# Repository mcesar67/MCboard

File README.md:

# MCboard

A parametric solderable protoboard. A Python script writes the KiCad project and the files a PCB fab needs, for any
number of rows and columns. A second script takes a board with the parts of a circuit placed on it, and says which
solder jumpers to close and which wires to add.

| Top | Bottom | Top with `--top smt` |
|---|---|---|
|  |  |  |

*A 14x13 board, rendered by KiCad.*

**Status.** The output passes KiCad's DRC against the fab rules, and the Gerbers match KiCad's own export. See
[Limits](#limits).

**[User manual](docs/MANUAL.md)**: generating a board, and planning a circuit on it, step by step.

## The pattern

Like a breadboard, but soldered, and every connection between groups is your choice. By default the pattern repeats
every 6 rows:

```text
       1   2   3   4
  A    o---o---o---o---   bus: one horizontal track across the board
       x   x   x   x      chevron solder jumper, open until you bridge it
  B    o   o   o   o      2-contact group
  C    o   o   o   o        a vertical strip per column
       x   x   x   x
  D    o   o   o   o      3-contact group
  E    o   o   o   o        a vertical strip per column
  F    o   o   o   o
       x   x   x   x
  G    o---o---o---o---   the next bus
```

Close a 2-3 chevron and the two groups become a strip of 5, as on a breadboard; close the others to reach a bus. All
tracks are on the bottom side, under solder mask. `--pattern` sets other arrangements, such as `b+5`, `b+3+2+2b+5` or
`classic`, a breadboard with two rails; `--top smt` adds chevrons and islands on the top side for SMD parts. See
[the manual](docs/MANUAL.md#15-row-pattern).

## Quick start

You need Python 3 and nothing else; KiCad is needed only to check the board or place a circuit on it.

```bash
cd protoboard_generator
python3 generate_protoboard.py --cols 30 --rows 61 --fab jlcpcb
```

This writes the KiCad project, a zip for the fab and an A4 PDF of both sides, like those in [`examples/`](examples/). Upload the zip and order a **2-layer
board, 1 oz copper**.

To plan a circuit, generate the board with `--working-copy`, which also writes `<name>_working.kicad_pcb`. In KiCad,
update that file from your schematic, place the parts with their pins on the holes, save, and run:

```bash
python3 plan_board.py <folder>/<name>_working.kicad_pcb
```

It prints which chevrons to close and which wires to add, and writes a PDF with both sides marked. The same is
available as a button in KiCad's PCB editor, installed with `python3 install_kicad_plugin.py`, and a second button
applies the plan to the working copy, so that KiCad's ratsnest shows what is left to wire. A third clears both, and a
fourth, for wiring by hand, updates the ratsnest after each chevron or wire you draw yourself, without planning. They
are described in [the manual](docs/MANUAL.md#21-what-the-plan-gives-you).

Everything else, options, mounting holes, checking a board, reading the plan and drawing part of the wiring yourself,
is in the [user manual](docs/MANUAL.md).

## Limits

- With `--top smt`, excess solder can close a chevron hidden under a part.
- The planner is a heuristic: it always gives the same plan for the same board, but that plan may not have the fewest
  wires or chevrons, and placement decides whether a plan exists at all.
- The KiCad buttons need KiCad 9.0 or later with its API turned on, and fetch the `kicad-python` package the first
  time. They have been tried on KiCad 9 and 10, on Linux and Windows 11, but not on macOS.
- Text in very dense characters, such as CJK at 1 mm, may fill in when printed.
- There is no automated test suite yet.

## Repository layout

| Path | Contents |
|---|---|
| `protoboard_generator/generate_protoboard.py` | The generator's entry point |
| `protoboard_generator/plan_board.py` | The planner's entry point |
| `protoboard_generator/install_kicad_plugin.py`, `kicad_plugin/` | The KiCad buttons |
| `protoboard_generator/protoboard/` | The code. Its `__init__.py` is the reading guide |
| `protoboard_generator/rules/`, `fonts/` | Fab rules and the stroke font, see `NOTICE.md` |
| `examples/` | Generated boards ready to open or order: a classic breadboard, the default, and the default with `--top smt` |
| `tests/t555/` | Test boards for the planner: a 555 circuit, imported and placed |
| `docs/MANUAL.md` | User manual: generating a board, then planning a circuit |
| `docs/DESIGN.md` | Design notes: why the pattern is what it is, every dimension, what was rejected, how to check changes |

## Licence

Copyright (C) 2026 [mcesar67](https://github.com/mcesar67).

The code and documentation were written with the help of Claude (Anthropic), under the author's direction.

GPL-3.0-or-later, see [`LICENSE`](LICENSE). Third-party material and its licences are listed in [`NOTICE.md`](NOTICE.md).
There is no warranty of any kind: check a board before you pay for it.

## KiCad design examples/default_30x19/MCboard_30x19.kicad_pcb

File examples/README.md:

# Examples

Boards generated as they are, ready to open in KiCad or to order. Each folder has the KiCad project, the zip for the fab
and the A4 drawing. They were made with `--fab generic`, the default, which satisfies both JLCPCB and PCBWay, and
are in KiCad 10 format; add `--kicad 9` to the commands below for KiCad 9.

| Folder | Board | Size |
|---|---|---|
| `classic_64x20/` | A classic breadboard: two rails at each edge, two strips of 5 per column, no mounting holes | 170.02 x 58.26 mm |
| `default_30x19/` | The default pattern, a hole in each corner, `--silk outline` | 81.66 x 62.72 mm |
| `smt_30x19/` | The same with `--top smt`, with the default `--silk bars` | 81.66 x 62.72 mm |

To make them again, from the `protoboard_generator` folder:

```bash
python3 generate_protoboard.py --cols 64 --rows 20 --pattern classic --no-mount-holes --margin-plain 5 -o ../examples/classic_64x20/
python3 generate_protoboard.py --cols 30 --rows 19 --mount-x 2 --mount-y 0 --silk outline -o ../examples/default_30x19/
python3 generate_protoboard.py --cols 30 --rows 19 --mount-x 2 --mount-y 0 --top smt -o ../examples/smt_30x19/
```

`--margin-plain 5` makes room for the name, which does not fit in the 4 mm margin of a board with no mounting holes.
`--mount-x 2 --mount-y 0` puts two holes on the top and bottom sides and none on the others, so they end up in the
corners. The options are explained in the [user manual](../docs/MANUAL.md).

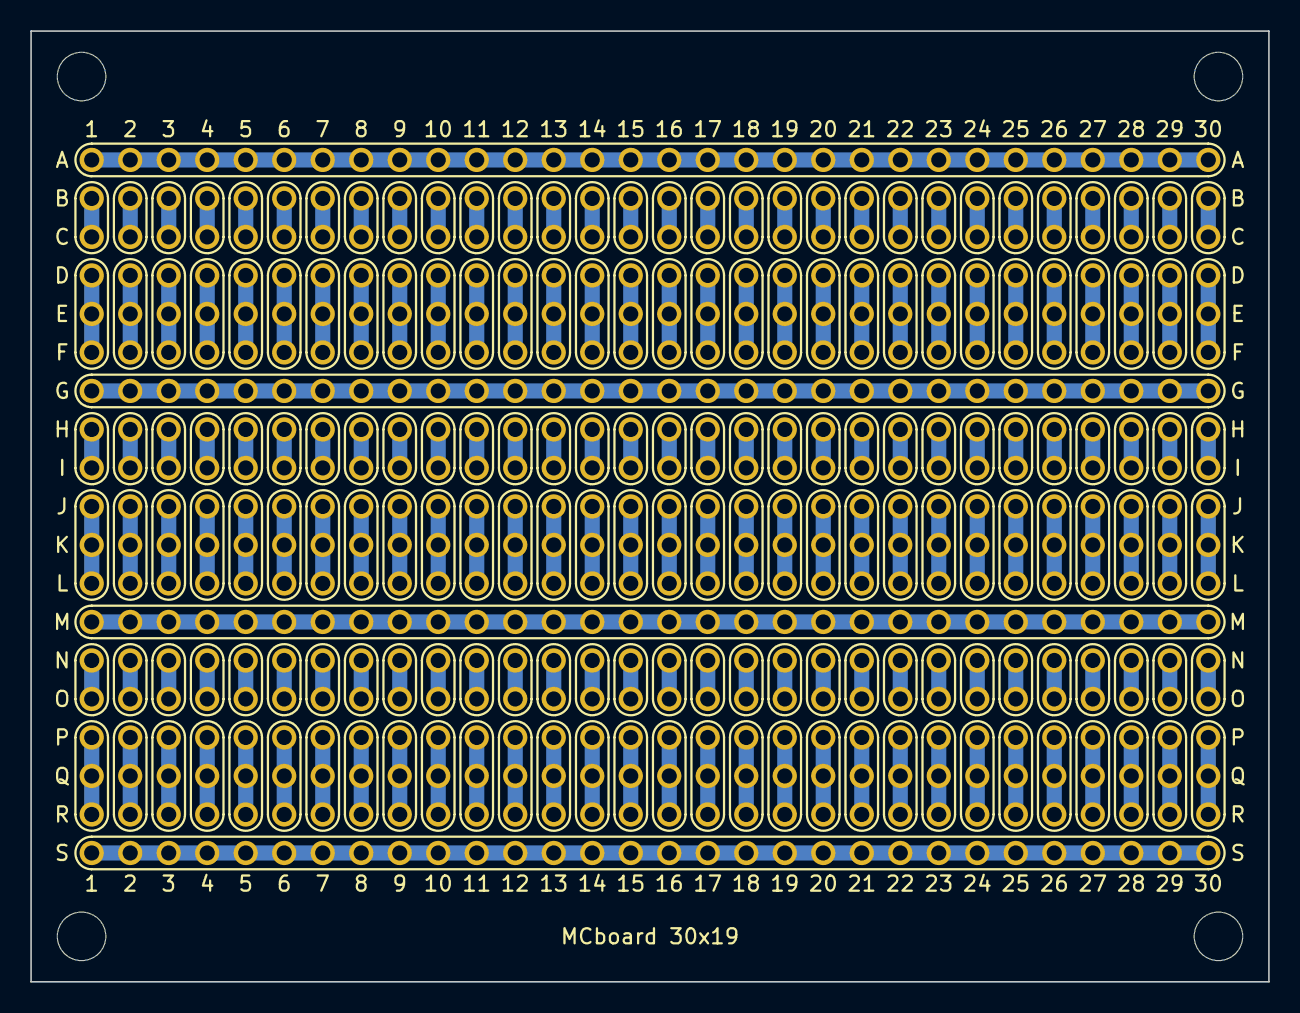
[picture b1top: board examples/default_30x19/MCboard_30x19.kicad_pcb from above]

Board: 2 copper layers, 81.7 x 62.7 mm, 844 parts (0 on the bottom side), 184 nets.

Parts:
PBH1, PBH2, PBH3, PBH4, PBH5, PBH6, PBH7, PBH8, PBH9, PBH10, PBH11, PBH12, PBH13, PBH14, PBH15, PBH16, PBH17, PBH18, PBH19, PBH20, PBH21, PBH22, PBH23, PBH24, PBH25, PBH26, PBH27, PBH28, PBH29, PBH30, PBH31, PBH32, PBH33, PBH34, PBH35, PBH36, PBH37, PBH38, PBH39, PBH40, PBH41, PBH42, PBH43, PBH44, PBH45, PBH46, PBH47, PBH48, PBH49, PBH50, PBH51, PBH52, PBH53, PBH54, PBH55, PBH56, PBH57, PBH58, PBH59, PBH60, PBH61, PBH62, PBH63, PBH64, PBH65, PBH66, PBH67, PBH68, PBH69, PBH70, PBH71, PBH72, PBH73, PBH74, PBH75, PBH76, PBH77, PBH78, PBH79, PBH80, PBH81, PBH82, PBH83, PBH84, PBH85, PBH86, PBH87, PBH88, PBH89, PBH90, PBH91, PBH92, PBH93, PBH94, PBH95, PBH96, PBH97, PBH98, PBH99, PBH100, PBH101, PBH102, PBH103, PBH104, PBH105, PBH106, PBH107, PBH108, PBH109, PBH110, PBH111, PBH112, PBH113, PBH114, PBH115, PBH116, PBH117, PBH118, PBH119, PBH120, PBH121, PBH122, PBH123, PBH124, PBH125, PBH126, PBH127, PBH128, PBH129, PBH130, PBH131, PBH132, PBH133, PBH134, PBH135, PBH136, PBH137, PBH138, PBH139, PBH140, PBH141, PBH142, PBH143, PBH144, PBH145, PBH146, PBH147, PBH148, PBH149, PBH150, PBH151, PBH152, PBH153, PBH154, PBH155, PBH156, PBH157, PBH158, PBH159, PBH160, PBH161, PBH162, PBH163, PBH164, PBH165, PBH166, PBH167, PBH168, PBH169, PBH170, PBH171, PBH172, PBH173, PBH174, PBH175, PBH176, PBH177, PBH178, PBH179, PBH180, PBH181, PBH182, PBH183, PBH184, PBH185, PBH186, PBH187, PBH188, PBH189, PBH190, PBH191, PBH192, PBH193, PBH194, PBH195, PBH196, PBH197, PBH198, PBH199, PBH200, PBH201, PBH202, PBH203, PBH204, PBH205, PBH206, PBH207, PBH208, PBH209, PBH210, PBH211, PBH212, PBH213, PBH214, PBH215, PBH216, PBH217, PBH218, PBH219, PBH220, PBH221, PBH222, PBH223, PBH224, PBH225, PBH226, PBH227, PBH228, PBH229, PBH230, PBH231, PBH232, PBH233, PBH234, PBH235, PBH236, PBH237, PBH238, PBH239, PBH240, PBH241, PBH242, PBH243, PBH244, PBH245, PBH246, PBH247, PBH248, PBH249, PBH250, PBH251, PBH252, PBH253, PBH254, PBH255, PBH256, PBH257, PBH258, PBH259, PBH260, PBH261, PBH262, PBH263, PBH264, PBH265, PBH266, PBH267, PBH268, PBH269, PBH270, PBH271, PBH272, PBH273, PBH274, PBH275, PBH276, PBH277, PBH278, PBH279, PBH280, PBH281, PBH282, PBH283, PBH284, PBH285, PBH286, PBH287, PBH288, PBH289, PBH290, PBH291, PBH292, PBH293, PBH294, PBH295, PBH296, PBH297, PBH298, PBH299, PBH300, PBH301, PBH302, PBH303, PBH304, PBH305, PBH306, PBH307, PBH308, PBH309, PBH310, PBH311, PBH312, PBH313, PBH314, PBH315, PBH316, PBH317, PBH318, PBH319, PBH320, PBH321, PBH322, PBH323, PBH324, PBH325, PBH326, PBH327, PBH328, PBH329, PBH330, PBH331, PBH332, PBH333, PBH334, PBH335, PBH336, PBH337, PBH338, PBH339, PBH340, PBH341, PBH342, PBH343, PBH344, PBH345, PBH346, PBH347, PBH348, PBH349, PBH350, PBH351, PBH352, PBH353, PBH354, PBH355, PBH356, PBH357, PBH358, PBH359, PBH360, PBH361, PBH362, PBH363, PBH364, PBH365, PBH366, PBH367, PBH368, PBH369, PBH370, PBH371, PBH372, PBH373, PBH374, PBH375, PBH376, PBH377, PBH378, PBH379, PBH380, PBH381, PBH382, PBH383, PBH384, PBH385, PBH386, PBH387, PBH388, PBH389, PBH390, PBH391, PBH392, PBH393, PBH394, PBH395, PBH396, PBH397, PBH398, PBH399, PBH400, PBH401, PBH402, PBH403, PBH404, PBH405, PBH406, PBH407, PBH408, PBH409, PBH410, PBH411, PBH412, PBH413, PBH414, PBH415, PBH416, PBH417, PBH418, PBH419, PBH420, PBH421, PBH422, PBH423, PBH424, PBH425, PBH426, PBH427, PBH428, PBH429, PBH430, PBH431, PBH432, PBH433, PBH434, PBH435, PBH436, PBH437, PBH438, PBH439, PBH440, PBH441, PBH442, PBH443, PBH444, PBH445, PBH446, PBH447, PBH448, PBH449, PBH450, PBH451, PBH452, PBH453, PBH454, PBH455, PBH456, PBH457, PBH458, PBH459, PBH460, PBH461, PBH462, PBH463, PBH464, PBH465, PBH466, PBH467, PBH468, PBH469, PBH470, PBH471, PBH472, PBH473, PBH474, PBH475, PBH476, PBH477, PBH478, PBH479, PBH480, PBH481, PBH482, PBH483, PBH484, PBH485, PBH486, PBH487, PBH488, PBH489, PBH490, PBH491, PBH492, PBH493, PBH494, PBH495, PBH496, PBH497, PBH498, PBH499, PBH500, PBH501, PBH502, PBH503, PBH504, PBH505, PBH506, PBH507, PBH508, PBH509, PBH510, PBH511, PBH512, PBH513, PBH514, PBH515, PBH516, PBH517, PBH518, PBH519, PBH520, PBH521, PBH522, PBH523, PBH524, PBH525, PBH526, PBH527, PBH528, PBH529, PBH530, PBH531, PBH532, PBH533, PBH534, PBH535, PBH536, PBH537, PBH538, PBH539, PBH540, PBH541, PBH542, PBH543, PBH544, PBH545, PBH546, PBH547, PBH548, PBH549, PBH550, PBH551, PBH552, PBH553, PBH554, PBH555, PBH556, PBH557, PBH558, PBH559, PBH560, PBH561, PBH562, PBH563, PBH564, PBH565, PBH566, PBH567, PBH568, PBH569, PBH570: hole; Hole
PBJP1, PBJP2, PBJP3, PBJP4, PBJP5, PBJP6, PBJP7, PBJP8, PBJP9, PBJP10, PBJP11, PBJP12, PBJP13, PBJP14, PBJP15, PBJP16, PBJP17, PBJP18, PBJP19, PBJP20, PBJP21, PBJP22, PBJP23, PBJP24, PBJP25, PBJP26, PBJP27, PBJP28, PBJP29, PBJP30, PBJP31, PBJP32, PBJP33, PBJP34, PBJP35, PBJP36, PBJP37, PBJP38, PBJP39, PBJP40, PBJP41, PBJP42, PBJP43, PBJP44, PBJP45, PBJP46, PBJP47, PBJP48, PBJP49, PBJP50, PBJP51, PBJP52, PBJP53, PBJP54, PBJP55, PBJP56, PBJP57, PBJP58, PBJP59, PBJP60, PBJP61, PBJP62, PBJP63, PBJP64, PBJP65, PBJP66, PBJP67, PBJP68, PBJP69, PBJP70, PBJP71, PBJP72, PBJP73, PBJP74, PBJP75, PBJP76, PBJP77, PBJP78, PBJP79, PBJP80, PBJP81, PBJP82, PBJP83, PBJP84, PBJP85, PBJP86, PBJP87, PBJP88, PBJP89, PBJP90, PBJP91, PBJP92, PBJP93, PBJP94, PBJP95, PBJP96, PBJP97, PBJP98, PBJP99, PBJP100, PBJP101, PBJP102, PBJP103, PBJP104, PBJP105, PBJP106, PBJP107, PBJP108, PBJP109, PBJP110, PBJP111, PBJP112, PBJP113, PBJP114, PBJP115, PBJP116, PBJP117, PBJP118, PBJP119, PBJP120, PBJP121, PBJP122, PBJP123, PBJP124, PBJP125, PBJP126, PBJP127, PBJP128, PBJP129, PBJP130, PBJP131, PBJP132, PBJP133, PBJP134, PBJP135, PBJP136, PBJP137, PBJP138, PBJP139, PBJP140, PBJP141, PBJP142, PBJP143, PBJP144, PBJP145, PBJP146, PBJP147, PBJP148, PBJP149, PBJP150, PBJP151, PBJP152, PBJP153, PBJP154, PBJP155, PBJP156, PBJP157, PBJP158, PBJP159, PBJP160, PBJP161, PBJP162, PBJP163, PBJP164, PBJP165, PBJP166, PBJP167, PBJP168, PBJP169, PBJP170, PBJP171, PBJP172, PBJP173, PBJP174, PBJP175, PBJP176, PBJP177, PBJP178, PBJP179, PBJP180, PBJP181, PBJP182, PBJP183, PBJP184, PBJP185, PBJP186, PBJP187, PBJP188, PBJP189, PBJP190, PBJP191, PBJP192, PBJP193, PBJP194, PBJP195, PBJP196, PBJP197, PBJP198, PBJP199, PBJP200, PBJP201, PBJP202, PBJP203, PBJP204, PBJP205, PBJP206, PBJP207, PBJP208, PBJP209, PBJP210, PBJP211, PBJP212, PBJP213, PBJP214, PBJP215, PBJP216, PBJP217, PBJP218, PBJP219, PBJP220, PBJP221, PBJP222, PBJP223, PBJP224, PBJP225, PBJP226, PBJP227, PBJP228, PBJP229, PBJP230, PBJP231, PBJP232, PBJP233, PBJP234, PBJP235, PBJP236, PBJP237, PBJP238, PBJP239, PBJP240, PBJP241, PBJP242, PBJP243, PBJP244, PBJP245, PBJP246, PBJP247, PBJP248, PBJP249, PBJP250, PBJP251, PBJP252, PBJP253, PBJP254, PBJP255, PBJP256, PBJP257, PBJP258, PBJP259, PBJP260, PBJP261, PBJP262, PBJP263, PBJP264, PBJP265, PBJP266, PBJP267, PBJP268, PBJP269, PBJP270: chevron; ChevronJumper
PBMH1, PBMH2, PBMH3, PBMH4: mounting hole; MountingHole

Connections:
BUS_R1: PBH1.1, PBH20.1, PBH39.1, PBH58.1, PBH77.1, PBH96.1, PBH115.1, PBH134.1, PBH153.1, PBH172.1, PBH191.1, PBH210.1, PBH229.1, PBH248.1, PBH267.1, PBH286.1, PBH305.1, PBH324.1, PBH343.1, PBH362.1, PBH381.1, PBH400.1, PBH419.1, PBH438.1, PBH457.1, PBH476.1, PBH495.1, PBH514.1, PBH533.1, PBH552.1, PBJP1.1, PBJP10.1, PBJP19.1, PBJP28.1, PBJP37.1, PBJP46.1, PBJP55.1, PBJP64.1, PBJP73.1, PBJP82.1, PBJP91.1, PBJP100.1, PBJP109.1, PBJP118.1, PBJP127.1, PBJP136.1, PBJP145.1, PBJP154.1, PBJP163.1, PBJP172.1, PBJP181.1, PBJP190.1, PBJP199.1, PBJP208.1, PBJP217.1, PBJP226.1, PBJP235.1, PBJP244.1, PBJP253.1, PBJP262.1
BUS_R7: PBH7.1, PBH26.1, PBH45.1, PBH64.1, PBH83.1, PBH102.1, PBH121.1, PBH140.1, PBH159.1, PBH178.1, PBH197.1, PBH216.1, PBH235.1, PBH254.1, PBH273.1, PBH292.1, PBH311.1, PBH330.1, PBH349.1, PBH368.1, PBH387.1, PBH406.1, PBH425.1, PBH444.1, PBH463.1, PBH482.1, PBH501.1, PBH520.1, PBH539.1, PBH558.1, PBJP3.2, PBJP4.1, PBJP12.2, PBJP13.1, PBJP21.2, PBJP22.1, PBJP30.2, PBJP31.1, PBJP39.2, PBJP40.1, PBJP48.2, PBJP49.1, PBJP57.2, PBJP58.1, PBJP66.2, PBJP67.1, PBJP75.2, PBJP76.1, PBJP84.2, PBJP85.1, PBJP93.2, PBJP94.1, PBJP102.2, PBJP103.1, PBJP111.2, PBJP112.1, PBJP120.2, PBJP121.1, PBJP129.2, PBJP130.1, PBJP138.2, PBJP139.1, PBJP147.2, PBJP148.1, PBJP156.2, PBJP157.1, PBJP165.2, PBJP166.1, PBJP174.2, PBJP175.1, PBJP183.2, PBJP184.1, PBJP192.2, PBJP193.1, PBJP201.2, PBJP202.1, PBJP210.2, PBJP211.1, PBJP219.2, PBJP220.1, PBJP228.2, PBJP229.1, PBJP237.2, PBJP238.1, PBJP246.2, PBJP247.1, PBJP255.2, PBJP256.1, PBJP264.2, PBJP265.1
BUS_R13: PBH13.1, PBH32.1, PBH51.1, PBH70.1, PBH89.1, PBH108.1, PBH127.1, PBH146.1, PBH165.1, PBH184.1, PBH203.1, PBH222.1, PBH241.1, PBH260.1, PBH279.1, PBH298.1, PBH317.1, PBH336.1, PBH355.1, PBH374.1, PBH393.1, PBH412.1, PBH431.1, PBH450.1, PBH469.1, PBH488.1, PBH507.1, PBH526.1, PBH545.1, PBH564.1, PBJP6.2, PBJP7.1, PBJP15.2, PBJP16.1, PBJP24.2, PBJP25.1, PBJP33.2, PBJP34.1, PBJP42.2, PBJP43.1, PBJP51.2, PBJP52.1, PBJP60.2, PBJP61.1, PBJP69.2, PBJP70.1, PBJP78.2, PBJP79.1, PBJP87.2, PBJP88.1, PBJP96.2, PBJP97.1, PBJP105.2, PBJP106.1, PBJP114.2, PBJP115.1, PBJP123.2, PBJP124.1, PBJP132.2, PBJP133.1, PBJP141.2, PBJP142.1, PBJP150.2, PBJP151.1, PBJP159.2, PBJP160.1, PBJP168.2, PBJP169.1, PBJP177.2, PBJP178.1, PBJP186.2, PBJP187.1, PBJP195.2, PBJP196.1, PBJP204.2, PBJP205.1, PBJP213.2, PBJP214.1, PBJP222.2, PBJP223.1, PBJP231.2, PBJP232.1, PBJP240.2, PBJP241.1, PBJP249.2, PBJP250.1, PBJP258.2, PBJP259.1, PBJP267.2, PBJP268.1
BUS_R19: PBH19.1, PBH38.1, PBH57.1, PBH76.1, PBH95.1, PBH114.1, PBH133.1, PBH152.1, PBH171.1, PBH190.1, PBH209.1, PBH228.1, PBH247.1, PBH266.1, PBH285.1, PBH304.1, PBH323.1, PBH342.1, PBH361.1, PBH380.1, PBH399.1, PBH418.1, PBH437.1, PBH456.1, PBH475.1, PBH494.1, PBH513.1, PBH532.1, PBH551.1, PBH570.1, PBJP9.2, PBJP18.2, PBJP27.2, PBJP36.2, PBJP45.2, PBJP54.2, PBJP63.2, PBJP72.2, PBJP81.2, PBJP90.2, PBJP99.2, PBJP108.2, PBJP117.2, PBJP126.2, PBJP135.2, PBJP144.2, PBJP153.2, PBJP162.2, PBJP171.2, PBJP180.2, PBJP189.2, PBJP198.2, PBJP207.2, PBJP216.2, PBJP225.2, PBJP234.2, PBJP243.2, PBJP252.2, PBJP261.2, PBJP270.2
C1_R2: PBH2.1, PBH3.1, PBJP1.2, PBJP2.1
C1_R4: PBH4.1, PBH5.1, PBH6.1, PBJP2.2, PBJP3.1
C1_R8: PBH8.1, PBH9.1, PBJP4.2, PBJP5.1
C1_R10: PBH10.1, PBH11.1, PBH12.1, PBJP5.2, PBJP6.1
C1_R14: PBH14.1, PBH15.1, PBJP7.2, PBJP8.1
C1_R16: PBH16.1, PBH17.1, PBH18.1, PBJP8.2, PBJP9.1
C2_R2: PBH21.1, PBH22.1, PBJP10.2, PBJP11.1
C2_R4: PBH23.1, PBH24.1, PBH25.1, PBJP11.2, PBJP12.1
C2_R8: PBH27.1, PBH28.1, PBJP13.2, PBJP14.1
C2_R10: PBH29.1, PBH30.1, PBH31.1, PBJP14.2, PBJP15.1
C2_R14: PBH33.1, PBH34.1, PBJP16.2, PBJP17.1
C2_R16: PBH35.1, PBH36.1, PBH37.1, PBJP17.2, PBJP18.1
C3_R2: PBH40.1, PBH41.1, PBJP19.2, PBJP20.1
C3_R4: PBH42.1, PBH43.1, PBH44.1, PBJP20.2, PBJP21.1
C3_R8: PBH46.1, PBH47.1, PBJP22.2, PBJP23.1
C3_R10: PBH48.1, PBH49.1, PBH50.1, PBJP23.2, PBJP24.1
C3_R14: PBH52.1, PBH53.1, PBJP25.2, PBJP26.1
C3_R16: PBH54.1, PBH55.1, PBH56.1, PBJP26.2, PBJP27.1
C4_R2: PBH59.1, PBH60.1, PBJP28.2, PBJP29.1
C4_R4: PBH61.1, PBH62.1, PBH63.1, PBJP29.2, PBJP30.1
C4_R8: PBH65.1, PBH66.1, PBJP31.2, PBJP32.1
C4_R10: PBH67.1, PBH68.1, PBH69.1, PBJP32.2, PBJP33.1
C4_R14: PBH71.1, PBH72.1, PBJP34.2, PBJP35.1
C4_R16: PBH73.1, PBH74.1, PBH75.1, PBJP35.2, PBJP36.1
C5_R2: PBH78.1, PBH79.1, PBJP37.2, PBJP38.1
C5_R4: PBH80.1, PBH81.1, PBH82.1, PBJP38.2, PBJP39.1
C5_R8: PBH84.1, PBH85.1, PBJP40.2, PBJP41.1
C5_R10: PBH86.1, PBH87.1, PBH88.1, PBJP41.2, PBJP42.1
C5_R14: PBH90.1, PBH91.1, PBJP43.2, PBJP44.1
C5_R16: PBH92.1, PBH93.1, PBH94.1, PBJP44.2, PBJP45.1
C6_R2: PBH97.1, PBH98.1, PBJP46.2, PBJP47.1
C6_R4: PBH99.1, PBH100.1, PBH101.1, PBJP47.2, PBJP48.1
C6_R8: PBH103.1, PBH104.1, PBJP49.2, PBJP50.1
C6_R10: PBH105.1, PBH106.1, PBH107.1, PBJP50.2, PBJP51.1
C6_R14: PBH109.1, PBH110.1, PBJP52.2, PBJP53.1
C6_R16: PBH111.1, PBH112.1, PBH113.1, PBJP53.2, PBJP54.1
C7_R2: PBH116.1, PBH117.1, PBJP55.2, PBJP56.1
C7_R4: PBH118.1, PBH119.1, PBH120.1, PBJP56.2, PBJP57.1
C7_R8: PBH122.1, PBH123.1, PBJP58.2, PBJP59.1
C7_R10: PBH124.1, PBH125.1, PBH126.1, PBJP59.2, PBJP60.1
C7_R14: PBH128.1, PBH129.1, PBJP61.2, PBJP62.1
C7_R16: PBH130.1, PBH131.1, PBH132.1, PBJP62.2, PBJP63.1
C8_R2: PBH135.1, PBH136.1, PBJP64.2, PBJP65.1
C8_R4: PBH137.1, PBH138.1, PBH139.1, PBJP65.2, PBJP66.1
C8_R8: PBH141.1, PBH142.1, PBJP67.2, PBJP68.1
C8_R10: PBH143.1, PBH144.1, PBH145.1, PBJP68.2, PBJP69.1
C8_R14: PBH147.1, PBH148.1, PBJP70.2, PBJP71.1
C8_R16: PBH149.1, PBH150.1, PBH151.1, PBJP71.2, PBJP72.1
C9_R2: PBH154.1, PBH155.1, PBJP73.2, PBJP74.1
C9_R4: PBH156.1, PBH157.1, PBH158.1, PBJP74.2, PBJP75.1
C9_R8: PBH160.1, PBH161.1, PBJP76.2, PBJP77.1
C9_R10: PBH162.1, PBH163.1, PBH164.1, PBJP77.2, PBJP78.1
C9_R14: PBH166.1, PBH167.1, PBJP79.2, PBJP80.1
C9_R16: PBH168.1, PBH169.1, PBH170.1, PBJP80.2, PBJP81.1
C10_R2: PBH173.1, PBH174.1, PBJP82.2, PBJP83.1
C10_R4: PBH175.1, PBH176.1, PBH177.1, PBJP83.2, PBJP84.1
C10_R8: PBH179.1, PBH180.1, PBJP85.2, PBJP86.1
C10_R10: PBH181.1, PBH182.1, PBH183.1, PBJP86.2, PBJP87.1
C10_R14: PBH185.1, PBH186.1, PBJP88.2, PBJP89.1
C10_R16: PBH187.1, PBH188.1, PBH189.1, PBJP89.2, PBJP90.1
C11_R2: PBH192.1, PBH193.1, PBJP91.2, PBJP92.1
C11_R4: PBH194.1, PBH195.1, PBH196.1, PBJP92.2, PBJP93.1
C11_R8: PBH198.1, PBH199.1, PBJP94.2, PBJP95.1
C11_R10: PBH200.1, PBH201.1, PBH202.1, PBJP95.2, PBJP96.1
C11_R14: PBH204.1, PBH205.1, PBJP97.2, PBJP98.1
C11_R16: PBH206.1, PBH207.1, PBH208.1, PBJP98.2, PBJP99.1
C12_R2: PBH211.1, PBH212.1, PBJP100.2, PBJP101.1
C12_R4: PBH213.1, PBH214.1, PBH215.1, PBJP101.2, PBJP102.1
C12_R8: PBH217.1, PBH218.1, PBJP103.2, PBJP104.1
C12_R10: PBH219.1, PBH220.1, PBH221.1, PBJP104.2, PBJP105.1
C12_R14: PBH223.1, PBH224.1, PBJP106.2, PBJP107.1
C12_R16: PBH225.1, PBH226.1, PBH227.1, PBJP107.2, PBJP108.1
C13_R2: PBH230.1, PBH231.1, PBJP109.2, PBJP110.1
C13_R4: PBH232.1, PBH233.1, PBH234.1, PBJP110.2, PBJP111.1
C13_R8: PBH236.1, PBH237.1, PBJP112.2, PBJP113.1
C13_R10: PBH238.1, PBH239.1, PBH240.1, PBJP113.2, PBJP114.1
C13_R14: PBH242.1, PBH243.1, PBJP115.2, PBJP116.1
C13_R16: PBH244.1, PBH245.1, PBH246.1, PBJP116.2, PBJP117.1
C14_R2: PBH249.1, PBH250.1, PBJP118.2, PBJP119.1
C14_R4: PBH251.1, PBH252.1, PBH253.1, PBJP119.2, PBJP120.1
C14_R8: PBH255.1, PBH256.1, PBJP121.2, PBJP122.1
C14_R10: PBH257.1, PBH258.1, PBH259.1, PBJP122.2, PBJP123.1
C14_R14: PBH261.1, PBH262.1, PBJP124.2, PBJP125.1
C14_R16: PBH263.1, PBH264.1, PBH265.1, PBJP125.2, PBJP126.1
C15_R2: PBH268.1, PBH269.1, PBJP127.2, PBJP128.1
C15_R4: PBH270.1, PBH271.1, PBH272.1, PBJP128.2, PBJP129.1
C15_R8: PBH274.1, PBH275.1, PBJP130.2, PBJP131.1
C15_R10: PBH276.1, PBH277.1, PBH278.1, PBJP131.2, PBJP132.1
C15_R14: PBH280.1, PBH281.1, PBJP133.2, PBJP134.1
C15_R16: PBH282.1, PBH283.1, PBH284.1, PBJP134.2, PBJP135.1
C16_R2: PBH287.1, PBH288.1, PBJP136.2, PBJP137.1
C16_R4: PBH289.1, PBH290.1, PBH291.1, PBJP137.2, PBJP138.1
C16_R8: PBH293.1, PBH294.1, PBJP139.2, PBJP140.1
C16_R10: PBH295.1, PBH296.1, PBH297.1, PBJP140.2, PBJP141.1
C16_R14: PBH299.1, PBH300.1, PBJP142.2, PBJP143.1
C16_R16: PBH301.1, PBH302.1, PBH303.1, PBJP143.2, PBJP144.1
C17_R2: PBH306.1, PBH307.1, PBJP145.2, PBJP146.1
C17_R4: PBH308.1, PBH309.1, PBH310.1, PBJP146.2, PBJP147.1
C17_R8: PBH312.1, PBH313.1, PBJP148.2, PBJP149.1
C17_R10: PBH314.1, PBH315.1, PBH316.1, PBJP149.2, PBJP150.1
C17_R14: PBH318.1, PBH319.1, PBJP151.2, PBJP152.1
C17_R16: PBH320.1, PBH321.1, PBH322.1, PBJP152.2, PBJP153.1
C18_R2: PBH325.1, PBH326.1, PBJP154.2, PBJP155.1
C18_R4: PBH327.1, PBH328.1, PBH329.1, PBJP155.2, PBJP156.1
C18_R8: PBH331.1, PBH332.1, PBJP157.2, PBJP158.1
C18_R10: PBH333.1, PBH334.1, PBH335.1, PBJP158.2, PBJP159.1
C18_R14: PBH337.1, PBH338.1, PBJP160.2, PBJP161.1
C18_R16: PBH339.1, PBH340.1, PBH341.1, PBJP161.2, PBJP162.1
C19_R2: PBH344.1, PBH345.1, PBJP163.2, PBJP164.1
C19_R4: PBH346.1, PBH347.1, PBH348.1, PBJP164.2, PBJP165.1
C19_R8: PBH350.1, PBH351.1, PBJP166.2, PBJP167.1
C19_R10: PBH352.1, PBH353.1, PBH354.1, PBJP167.2, PBJP168.1
C19_R14: PBH356.1, PBH357.1, PBJP169.2, PBJP170.1
C19_R16: PBH358.1, PBH359.1, PBH360.1, PBJP170.2, PBJP171.1
C20_R2: PBH363.1, PBH364.1, PBJP172.2, PBJP173.1
C20_R4: PBH365.1, PBH366.1, PBH367.1, PBJP173.2, PBJP174.1
C20_R8: PBH369.1, PBH370.1, PBJP175.2, PBJP176.1
C20_R10: PBH371.1, PBH372.1, PBH373.1, PBJP176.2, PBJP177.1
C20_R14: PBH375.1, PBH376.1, PBJP178.2, PBJP179.1
C20_R16: PBH377.1, PBH378.1, PBH379.1, PBJP179.2, PBJP180.1
C21_R2: PBH382.1, PBH383.1, PBJP181.2, PBJP182.1
C21_R4: PBH384.1, PBH385.1, PBH386.1, PBJP182.2, PBJP183.1
C21_R8: PBH388.1, PBH389.1, PBJP184.2, PBJP185.1
C21_R10: PBH390.1, PBH391.1, PBH392.1, PBJP185.2, PBJP186.1
C21_R14: PBH394.1, PBH395.1, PBJP187.2, PBJP188.1
C21_R16: PBH396.1, PBH397.1, PBH398.1, PBJP188.2, PBJP189.1
C22_R2: PBH401.1, PBH402.1, PBJP190.2, PBJP191.1
C22_R4: PBH403.1, PBH404.1, PBH405.1, PBJP191.2, PBJP192.1
C22_R8: PBH407.1, PBH408.1, PBJP193.2, PBJP194.1
C22_R10: PBH409.1, PBH410.1, PBH411.1, PBJP194.2, PBJP195.1
C22_R14: PBH413.1, PBH414.1, PBJP196.2, PBJP197.1
C22_R16: PBH415.1, PBH416.1, PBH417.1, PBJP197.2, PBJP198.1
C23_R2: PBH420.1, PBH421.1, PBJP199.2, PBJP200.1
C23_R4: PBH422.1, PBH423.1, PBH424.1, PBJP200.2, PBJP201.1
C23_R8: PBH426.1, PBH427.1, PBJP202.2, PBJP203.1
C23_R10: PBH428.1, PBH429.1, PBH430.1, PBJP203.2, PBJP204.1
C23_R14: PBH432.1, PBH433.1, PBJP205.2, PBJP206.1
C23_R16: PBH434.1, PBH435.1, PBH436.1, PBJP206.2, PBJP207.1
C24_R2: PBH439.1, PBH440.1, PBJP208.2, PBJP209.1
C24_R4: PBH441.1, PBH442.1, PBH443.1, PBJP209.2, PBJP210.1
C24_R8: PBH445.1, PBH446.1, PBJP211.2, PBJP212.1
C24_R10: PBH447.1, PBH448.1, PBH449.1, PBJP212.2, PBJP213.1
C24_R14: PBH451.1, PBH452.1, PBJP214.2, PBJP215.1
C24_R16: PBH453.1, PBH454.1, PBH455.1, PBJP215.2, PBJP216.1
C25_R2: PBH458.1, PBH459.1, PBJP217.2, PBJP218.1
C25_R4: PBH460.1, PBH461.1, PBH462.1, PBJP218.2, PBJP219.1
C25_R8: PBH464.1, PBH465.1, PBJP220.2, PBJP221.1
C25_R10: PBH466.1, PBH467.1, PBH468.1, PBJP221.2, PBJP222.1
C25_R14: PBH470.1, PBH471.1, PBJP223.2, PBJP224.1
C25_R16: PBH472.1, PBH473.1, PBH474.1, PBJP224.2, PBJP225.1
C26_R2: PBH477.1, PBH478.1, PBJP226.2, PBJP227.1
C26_R4: PBH479.1, PBH480.1, PBH481.1, PBJP227.2, PBJP228.1
C26_R8: PBH483.1, PBH484.1, PBJP229.2, PBJP230.1
C26_R10: PBH485.1, PBH486.1, PBH487.1, PBJP230.2, PBJP231.1
C26_R14: PBH489.1, PBH490.1, PBJP232.2, PBJP233.1
C26_R16: PBH491.1, PBH492.1, PBH493.1, PBJP233.2, PBJP234.1
C27_R2: PBH496.1, PBH497.1, PBJP235.2, PBJP236.1
C27_R4: PBH498.1, PBH499.1, PBH500.1, PBJP236.2, PBJP237.1
C27_R8: PBH502.1, PBH503.1, PBJP238.2, PBJP239.1
C27_R10: PBH504.1, PBH505.1, PBH506.1, PBJP239.2, PBJP240.1
C27_R14: PBH508.1, PBH509.1, PBJP241.2, PBJP242.1
C27_R16: PBH510.1, PBH511.1, PBH512.1, PBJP242.2, PBJP243.1
C28_R2: PBH515.1, PBH516.1, PBJP244.2, PBJP245.1
C28_R4: PBH517.1, PBH518.1, PBH519.1, PBJP245.2, PBJP246.1
C28_R8: PBH521.1, PBH522.1, PBJP247.2, PBJP248.1
C28_R10: PBH523.1, PBH524.1, PBH525.1, PBJP248.2, PBJP249.1
C28_R14: PBH527.1, PBH528.1, PBJP250.2, PBJP251.1
C28_R16: PBH529.1, PBH530.1, PBH531.1, PBJP251.2, PBJP252.1
C29_R2: PBH534.1, PBH535.1, PBJP253.2, PBJP254.1
C29_R4: PBH536.1, PBH537.1, PBH538.1, PBJP254.2, PBJP255.1
C29_R8: PBH540.1, PBH541.1, PBJP256.2, PBJP257.1
C29_R10: PBH542.1, PBH543.1, PBH544.1, PBJP257.2, PBJP258.1
C29_R14: PBH546.1, PBH547.1, PBJP259.2, PBJP260.1
C29_R16: PBH548.1, PBH549.1, PBH550.1, PBJP260.2, PBJP261.1
C30_R2: PBH553.1, PBH554.1, PBJP262.2, PBJP263.1
C30_R4: PBH555.1, PBH556.1, PBH557.1, PBJP263.2, PBJP264.1
C30_R8: PBH559.1, PBH560.1, PBJP265.2, PBJP266.1
C30_R10: PBH561.1, PBH562.1, PBH563.1, PBJP266.2, PBJP267.1
C30_R14: PBH565.1, PBH566.1, PBJP268.2, PBJP269.1
C30_R16: PBH567.1, PBH568.1, PBH569.1, PBJP269.2, PBJP270.1
